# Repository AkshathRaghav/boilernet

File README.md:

# BoilerNet: A Compute-Enabled Mini-NAS

<div align="center" style="display: flex; justify-content: center; align-items: center; gap: 1rem;">

</div>

<div class="caption" align="center">
    BoilerNet Team 20! 
    From L to R: Gokulkrishnan Harikrishnan, Akshath Raghav Ravikiran, Aneesh Reddy Poddutur, Gautum Kottayil Nambiar
</div>

## Overview 

This project aimed to develop a Network Attached Storage utilizing ESP32 MCUs. The aptly-named BoilerNet aims to enable In-Network-compute alongside swappable disks and compute workloads, neatly brought together by a cloud-hosted Dashboard interface. There are a few core ideas that form the foundation for this ”cluster” – Low Power Usage, Plug-and-Play Workloads, High Scalability.

> Our reports/presentations are linked in the [/docs](./docs/). They contain in-depth views, reasonings and explanations regarding the design and its motivation. We also outline how we tested and ensured functionality. **This repository is just meant to help anyone who wishes to "refer" to our code/designs for their own use-case.**

> Watch the Demo that won us the "Senior Design Award" for Spring '25 through Purdue ECE: [Link](https://www.youtube.com/watch?v=jUlh9KClEwE)!

<div style="display: flex; justify-content: center; align-items: center; gap: 1rem;">

</div>
<div class="caption" align="center">
    Top Level System Diagrams
</div>

## Mechanical Design

The physical enclosure consists of six piece types, along with an optional divider: 1x Enclosure Lid, 1x Enclosure Base, 8x compute Enclosures, 8x compute Enclosure Lids, 6x
3mm diameter - 20mm screws, 4x 3mm diameter - 5 mm screws. You can find the related CAD files at [/cad/](./cad/) w/o dependencies. Reach out to [Aneesh Poddutur](https://www.linkedin.com/in/aneesh-poddutur/) for more information. 

<div align="center">
  
  <caption> 
</div>
<div class="caption" align="center">
    Physical Enclosure
</div>

<div align="center">
  
</div>
<div class="caption" align="center">
    Top Enclosure
</div>

<div align="center">
  
</div>
<div class="caption" align="center">
    Compute Enclosure
</div>

<div align="center">
  
</div>
<div class="caption" align="center">
    Assembled System!
</div>

## PCB Design

This was our first time working on PCB Design, and had a few fly-wires hanging about. Below is one of the slides we usd in our [Final Presentation](/docs/Final%20Design%20Review.pdf) to sound endearing ;)

You can find our PCB Designs at [/gerbers/](./gerbers/) and [/kicad_projects](./kicad_projects/)! Reach out to [Gautam Nambiar](https://www.linkedin.com/in/gautam-nambiar-821479251/) and [Gokul Harikrishnan](https://www.linkedin.com/in/gokulkrishnan-harikrishnan-40334b227/) if you have any questions.

<div align="center">
  
</div>
<div class="caption" align="center">
    Network/Switch PCB
</div>

<div align="center">
  
</div>
<div class="caption" align="center">
    Compute Node PCB
</div>

<div align="center">
  
</div>
<div class="caption" align="center">
    Mishaps/Learnings!
</div>

## Software 

All the code for the MCUs are maintained within the [/src](./src/) folder. Each node's build is maintained within it's own ESP-IDF setup, and can be configured in isolation. 
[/model_train](./model_train/) contains the code for training the models and preparing weights to flashed through [./compute_nodes](./src/compute_nodes/). Please reach out to [Akshath Raghav](https://www.linkedin.com/in/akshathrr/) if you have any questions!

- [/src/fastapi_backend](./src/fastapi_backend/) and [/src/streamlit_frontend](./src/streamlit_frontend/) can be configured using the Makefiles. Try `make venv; make setup; make run`. 
- [/src/network_node](./src/network_node/), [/src/switch_nodes](./src/switch_nodes/) and [/src/compute_nodes](./src/compute_nodes/) require `idf.py` configured and `IDF_PATH` set up. Remember, `idf.py` should be run in an ESP-IDF project directory, i.e., a directory containing a CMakeLists.txt file. `idf.py fullclean; idf.py build; idf.py flash -port /dev/ttyUSB1` will be sufficient. 
- [/model_train/extract.sh](./model_train/extract.sh) has the script for setting up ImageNet -- only if you want to train your own subsets. Thanks to [BIGBALLON](https://gist.github.com/BIGBALLON) for this [script](https://gist.github.com/BIGBALLON/8a71d225eff18d88e469e6ea9b39cef4). 
- [/model_train/train.py](./model_train/train.py) and [/model_train/convert_and_header.py](./model_train/convert_and_header.py) will set you up quickly with training your MobileNet or EfficientNet backbones with a head for the subset you've chosen, and then quantizing them (w/ additional calibration tuning). Results will be put into [/model_train/models](./model_train/models/) and [/model_train/quantized_models](./model_train/quantized_models/). After you're done training, put the chosen header (.cc) file into [/src/compute_nodes/main](./src/compute_nodes/main/) and put this file name into Line 5 in [/src/compute_nodes/main/CMakeLists.txt](/src/compute_nodes/main/CMakeLists.txt). 

---

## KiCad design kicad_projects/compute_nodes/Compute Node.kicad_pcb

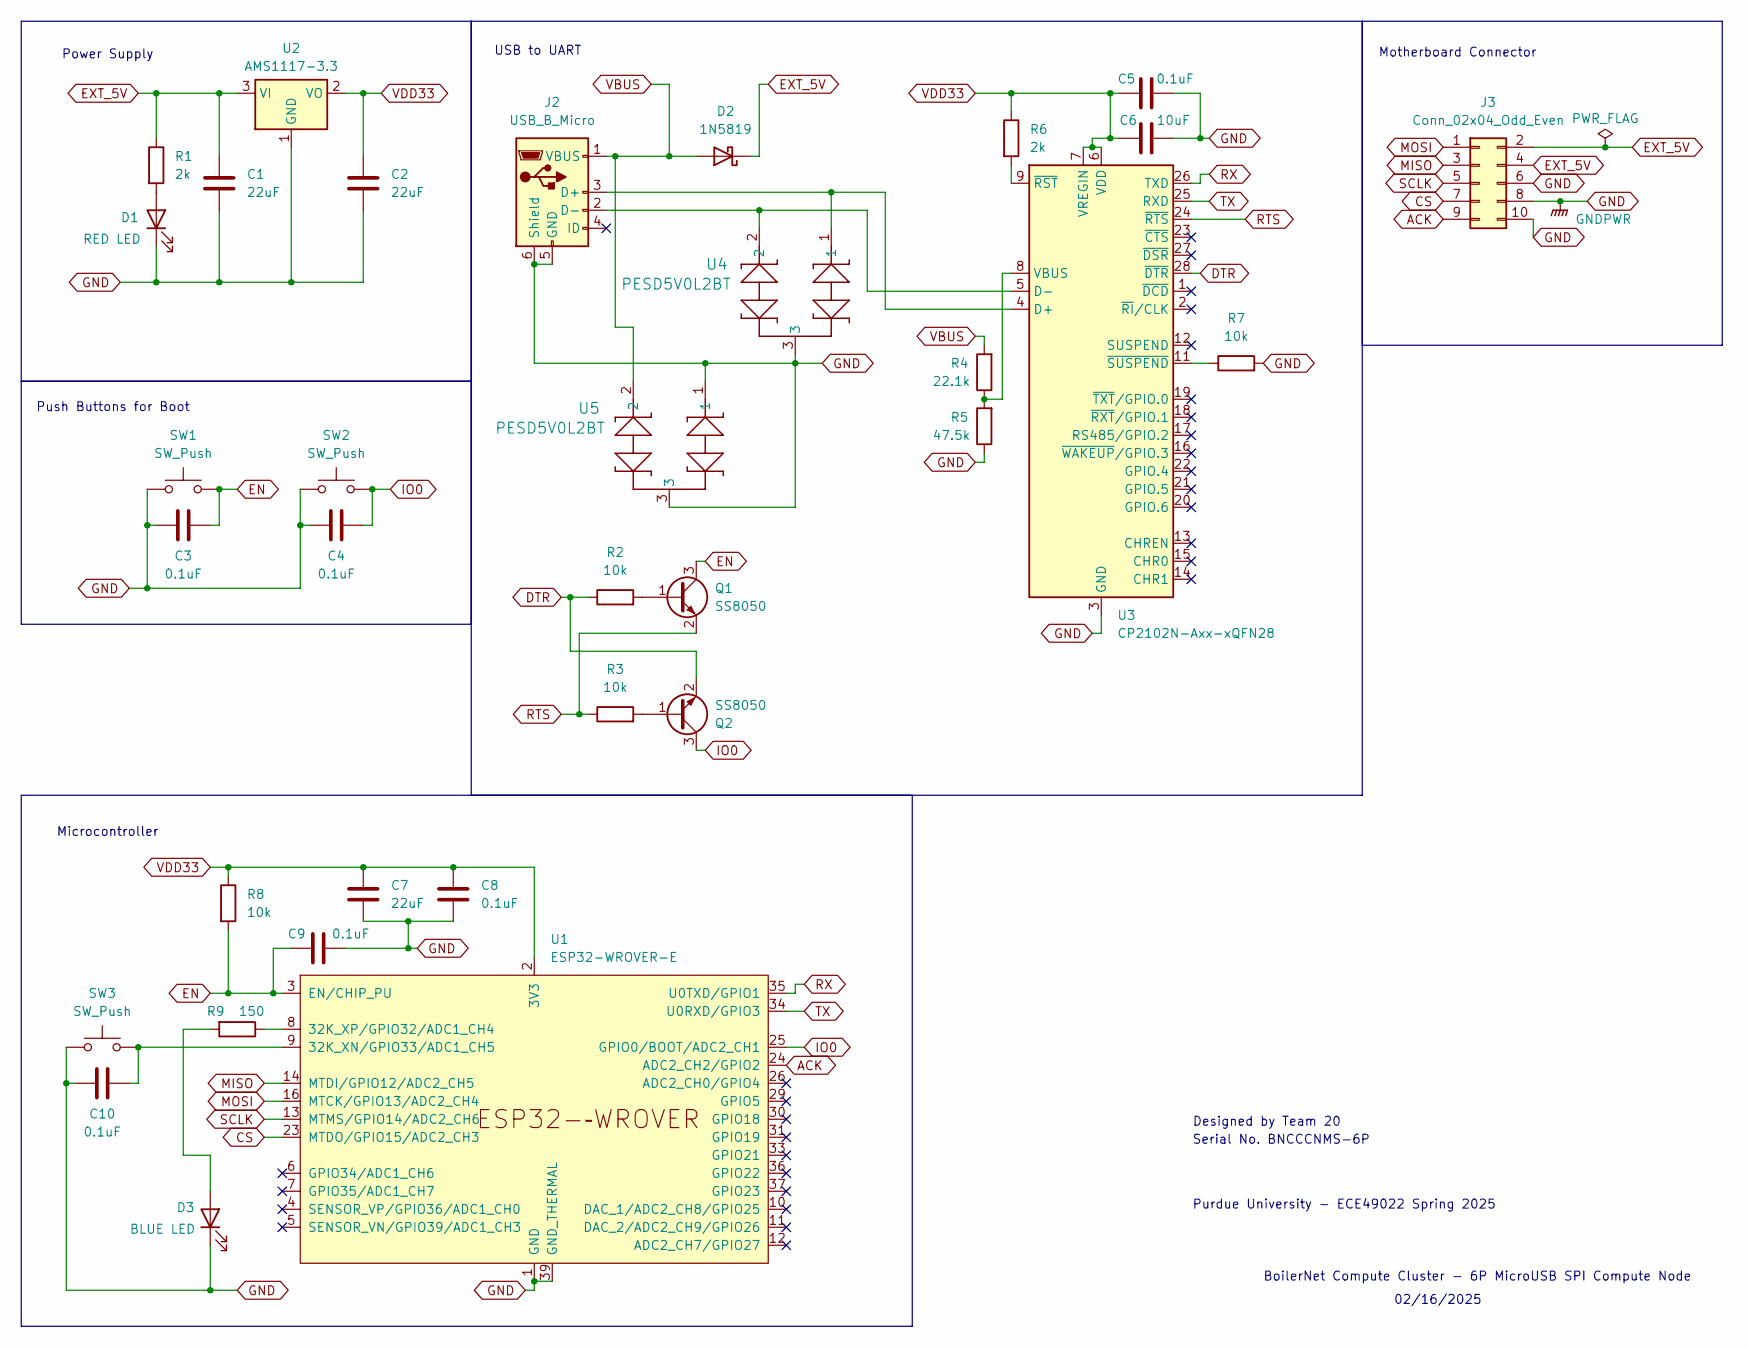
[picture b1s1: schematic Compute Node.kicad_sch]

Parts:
C1, C2, C7: 22uF; C_1206_3216Metric_Pad1.33x1.80mm_HandSolder
C3, C4, C5, C8, C9, C10: 0.1uF; C_1206_3216Metric_Pad1.33x1.80mm_HandSolder
C6: 10uF; C_1206_3216Metric_Pad1.33x1.80mm_HandSolder
D1: RED LED; LED_D4.0mm
D2: 1N5819; D_DO-41_SOD81_P10.16mm_Horizontal
D3: BLUE LED; LED_D4.0mm
J2: USB_B_Micro; USB_Micro-B_Amphenol_10118193-0002LF_Horizontal
J3: Conn_02x04_Odd_Even; PinHeader_2x05_P2.54mm_Horizontal
Q1, Q2: SS8050; SOT-23
R1, R6: 2k; R_1206_3216Metric_Pad1.30x1.75mm_HandSolder
R2, R3, R7, R8: 10k; R_1206_3216Metric_Pad1.30x1.75mm_HandSolder
R4: 22.1k; R_1206_3216Metric_Pad1.30x1.75mm_HandSolder
R5: 47.5k; R_1206_3216Metric_Pad1.30x1.75mm_HandSolder
R9: 150; R_1206_3216Metric_Pad1.30x1.75mm_HandSolder
SW1, SW2, SW3: SW_Push; SW_PUSH_6mm
U1: ESP32-WROVER-E
U2: AMS1117-3.3; SOT-223-3_TabPin2
U3: CP2102N-Axx-xQFN28; QFN-28-1EP_5x5mm_P0.5mm_EP3.35x3.35mm
U4, U5: PESD5V0L2BT; SOT23_NXP-M

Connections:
ACK: J3.9, U1.24 (ADC2_CH2/GPIO2)
CS: J3.7, U1.23 (MTDO/GPIO15/ADC2_CH3)
DTR: Q2.2 (E), R2.1, U3.28 (~DTR)
EN: C3.2, C9.2, Q1.3 (C), R8.2, SW1.2, U1.3 (EN/CHIP_PU)
EXT_5V: C1.1, D2.1 (K), J3.2, J3.4, R1.1, U2.3 (VI)
GND: C1.2, C2.2, C3.1, C4.1, C5.2, C6.2, C7.2, C8.2, C9.1, C10.1, D1.1 (K), D3.1 (K), J2.5 (GND), J2.6 (Shield), J3.6, J3.8, J3.10, R5.1, R7.2, SW1.1, SW2.1, SW3.1, U1.1 (GND), U1.15 (GND), U1.38 (GND), U1.39 (GND_THERMAL), U2.1 (GND), U3.3 (GND), U3.29 (GND), U4.3, U5.1, U5.3
IO0: C4.2, Q2.3 (C), SW2.2, U1.25 (GPIO0/BOOT/ADC2_CH1)
MISO: J3.3, U1.14 (MTDI/GPIO12/ADC2_CH5)
MOSI: J3.1, U1.16 (MTCK/GPIO13/ADC2_CH4)
unnamed: D1.2 (A), R1.2
unnamed: D3.2 (A), R9.2
unnamed: J2.3 (D+), U3.4 (D+), U4.1
unnamed: J2.2 (D-), U3.5 (D-), U4.2
unnamed: Q1.1 (B), R2.2
unnamed: Q2.1 (B), R3.2
unnamed: C10.2, SW3.2, U1.9 (32K_XN/GPIO33/ADC1_CH5)
unnamed: R9.1, U1.8 (32K_XP/GPIO32/ADC1_CH4)
unnamed: R4.1, R5.2, U3.8 (VBUS)
unnamed: R6.2, U3.9 (~RST)
unnamed: R7.1, U3.11 (~SUSPEND)
RTS: Q1.2 (E), R3.1, U3.24 (~RTS)
RX: U1.35 (U0TXD/GPIO1), U3.26 (TXD)
SCLK: J3.5, U1.13 (MTMS/GPIO14/ADC2_CH6)
TX: U1.34 (U0RXD/GPIO3), U3.25 (RXD)
VBUS: D2.2 (A), J2.1 (VBUS), R4.2, U5.2
VDD33: C2.1, C5.1, C6.1, C7.1, C8.1, R6.1, R8.1, U1.2 (3V3), U2.2 (VO), U3.6 (VDD), U3.7 (VREGIN)

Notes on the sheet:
Designed by Team 20
Motherboard Connector
Purdue University - ECE49022 Spring 2025
Microcontroller
USB to UART
Serial No. BNCCCNMS-6P
02/16/2025
Push Buttons for Boot
Power Supply
BoilerNet Compute Cluster - 6P MicroUSB SPI Compute Node

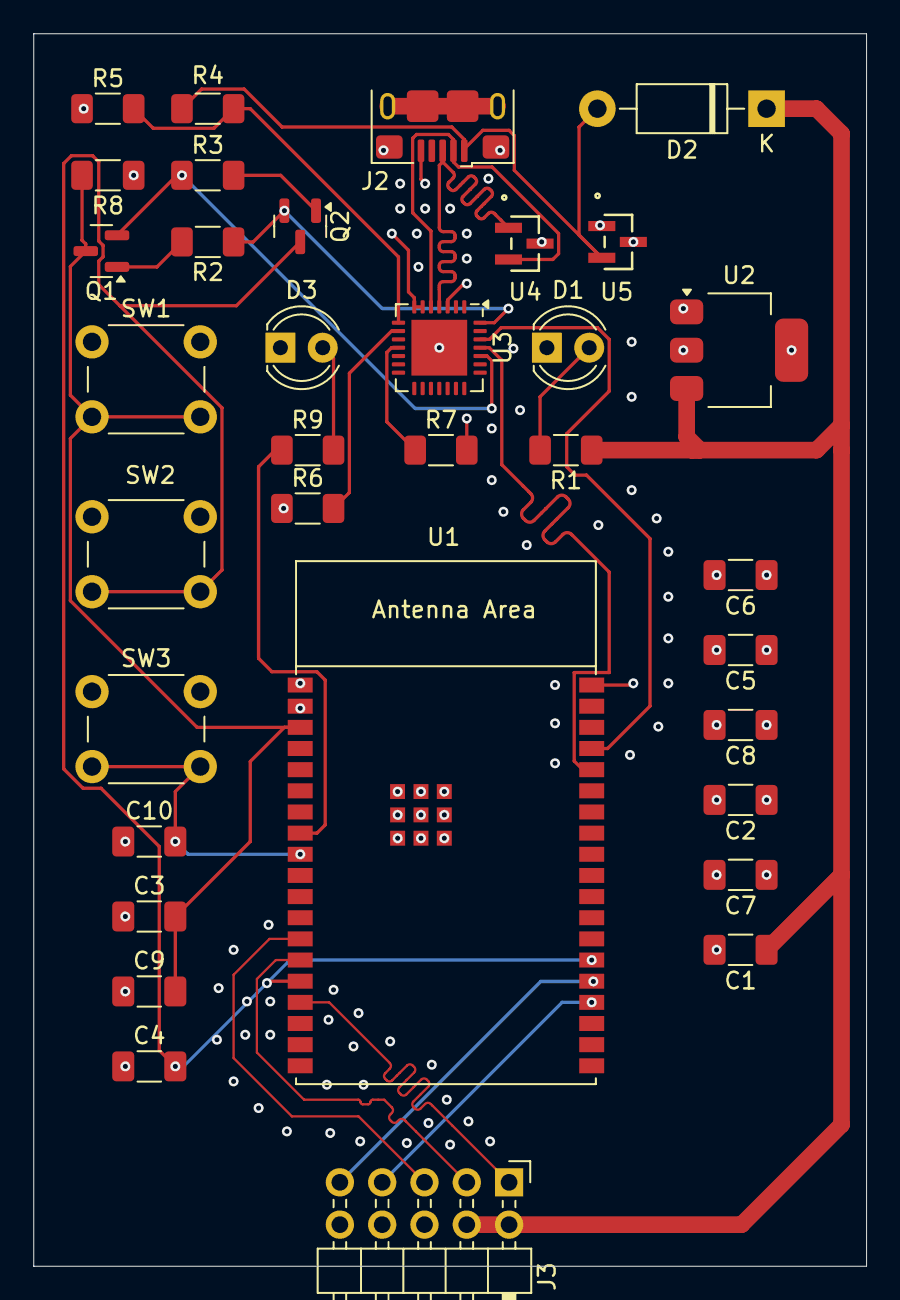
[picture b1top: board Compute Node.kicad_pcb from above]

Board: 4 copper layers, 50.0 x 74.0 mm, 34 parts (0 on the bottom side), 26 nets.

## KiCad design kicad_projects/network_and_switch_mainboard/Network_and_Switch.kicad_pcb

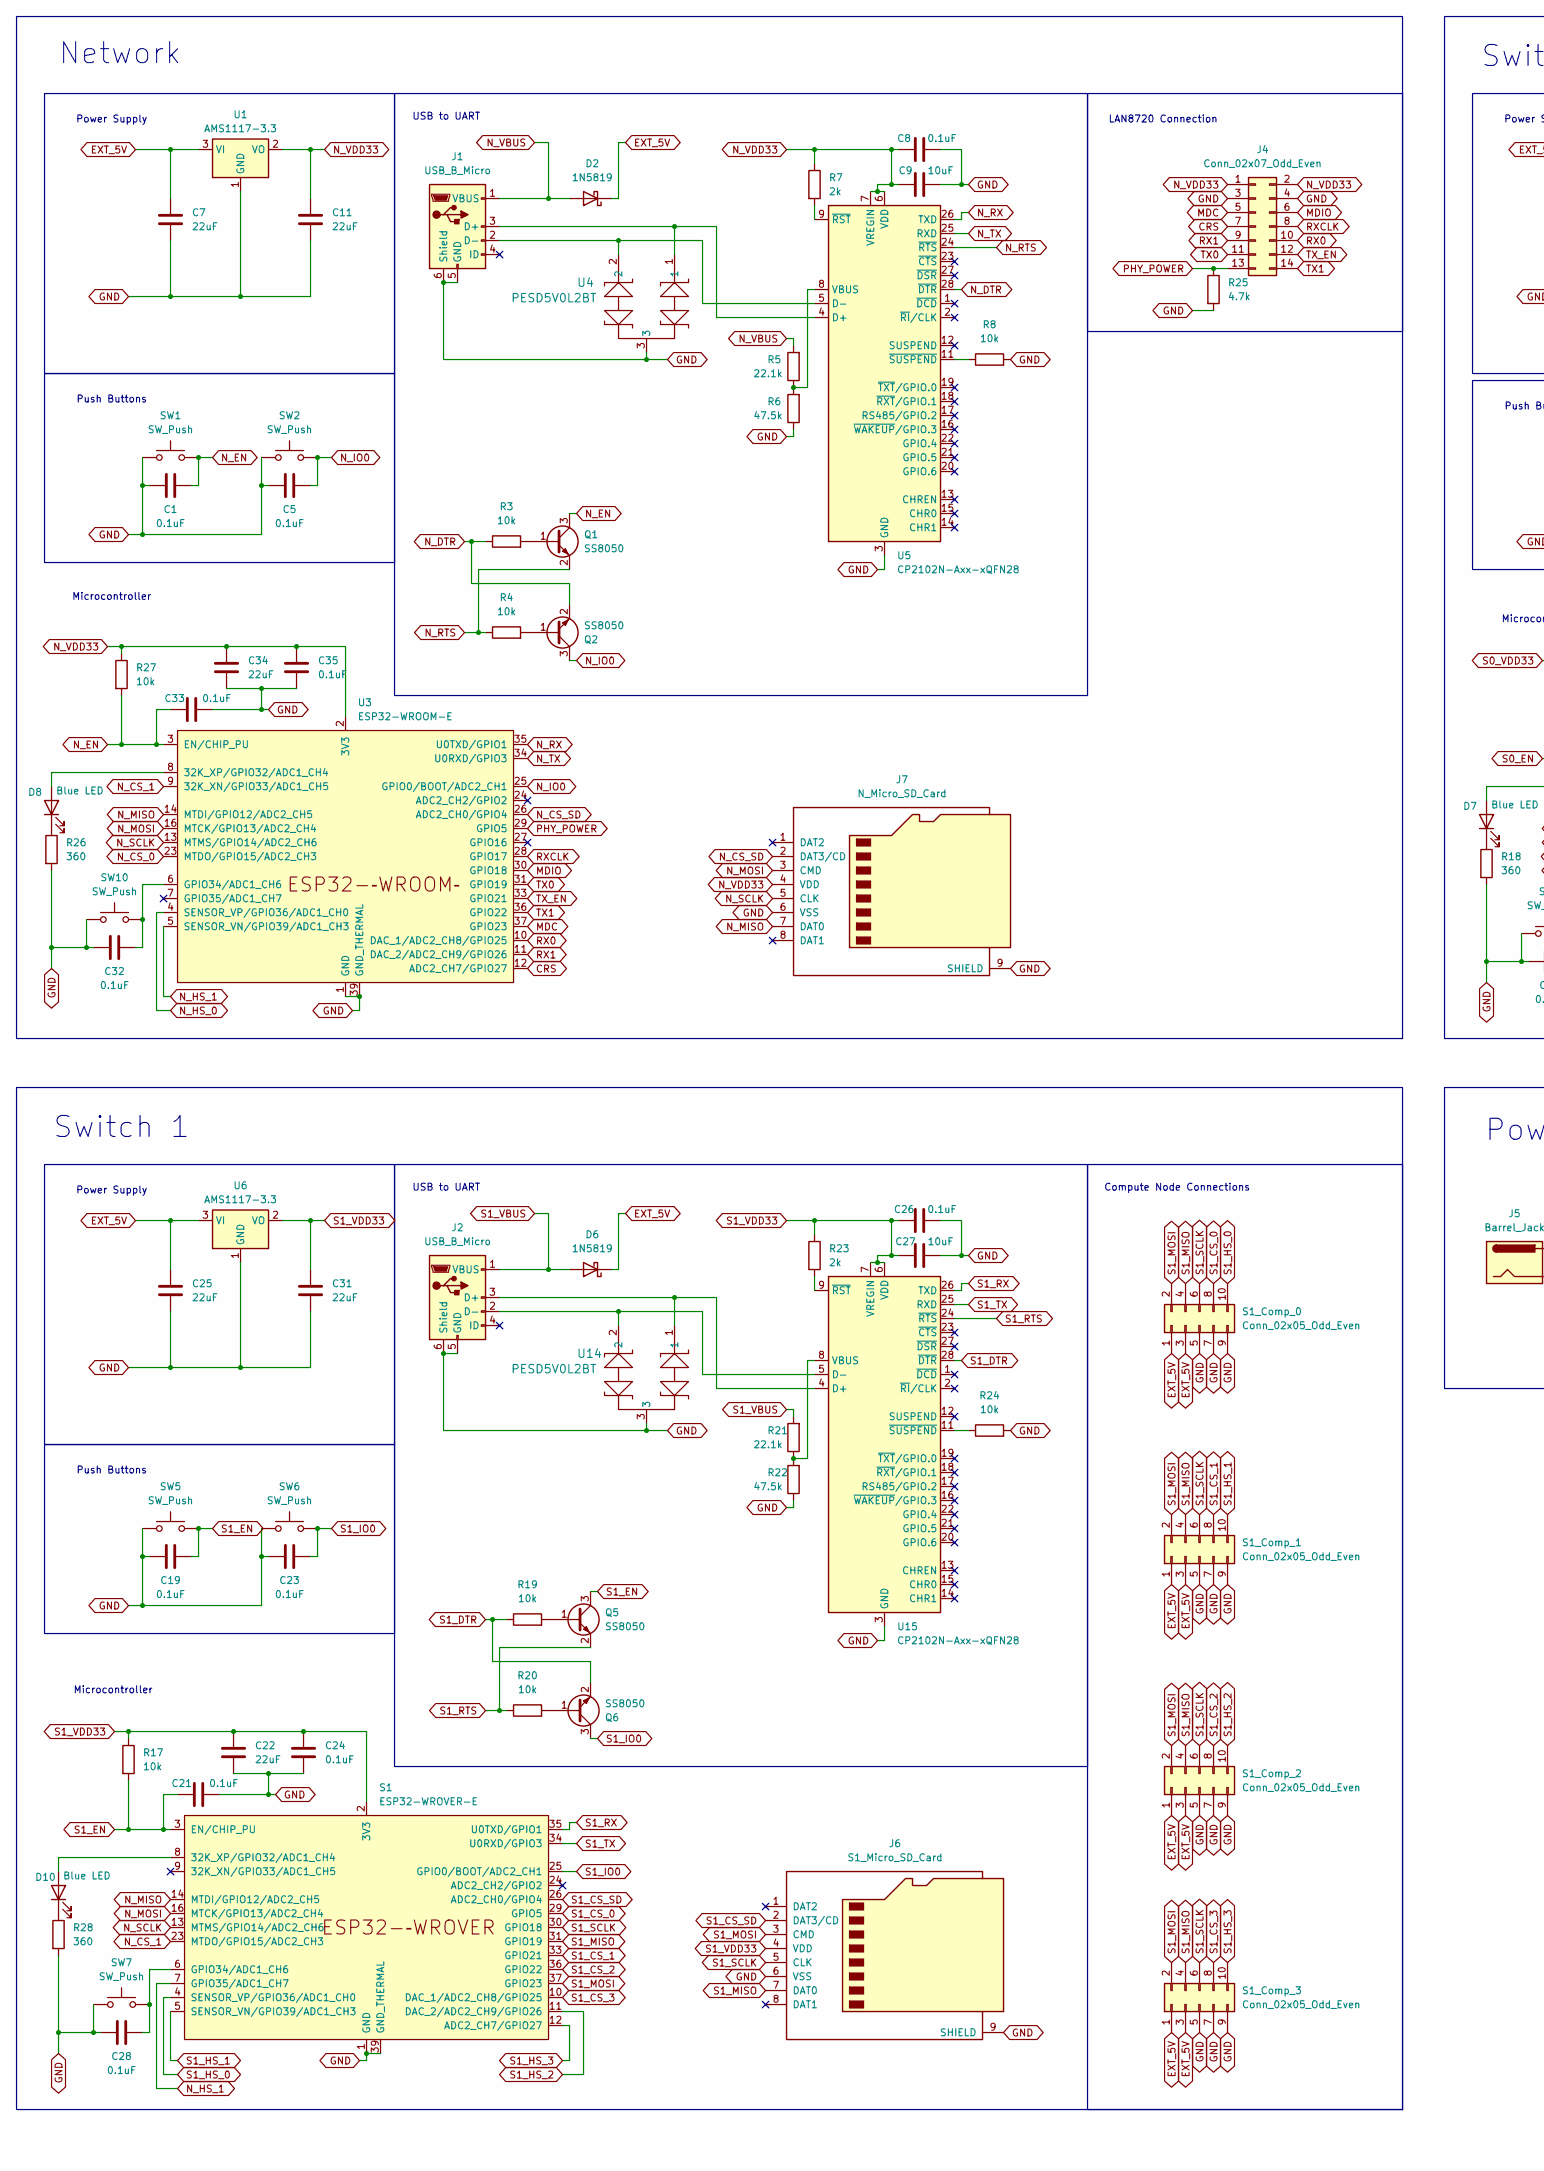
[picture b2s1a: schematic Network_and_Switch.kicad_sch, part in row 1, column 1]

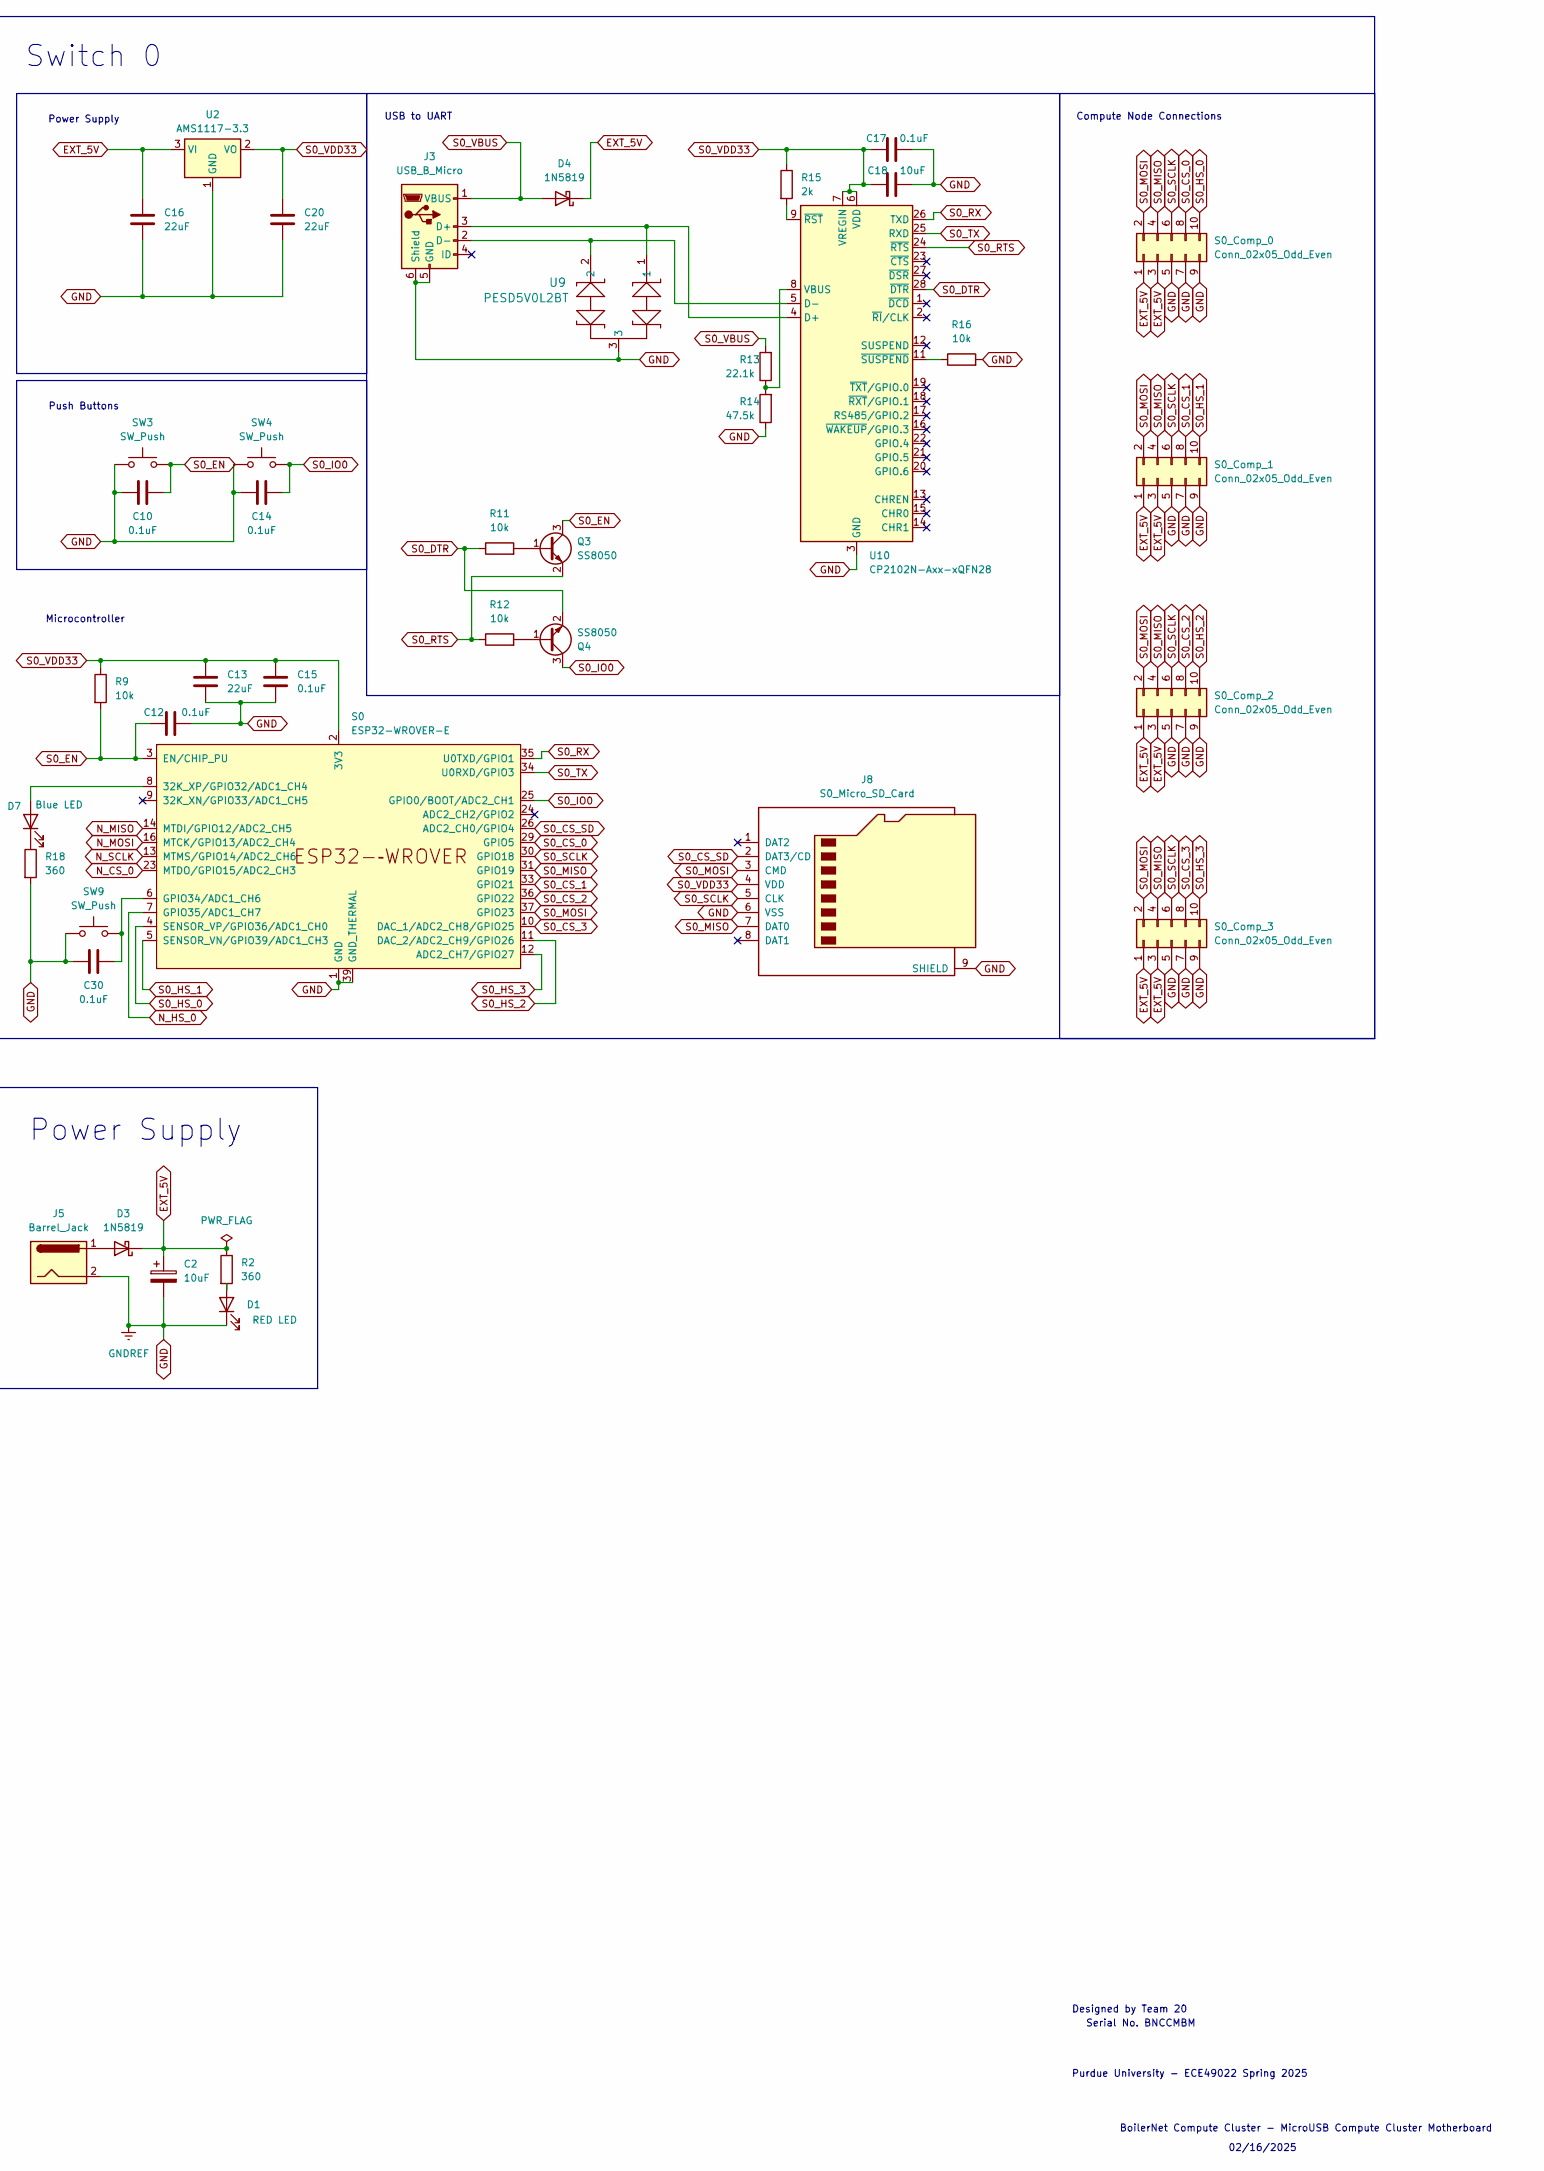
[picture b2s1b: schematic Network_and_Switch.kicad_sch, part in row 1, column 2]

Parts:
C1, C5, C8, C10, C12, C14, C15, C17, C19, C21, C23, C24, C26, C28, C30, C32, C33, C35: 0.1uF; C_1206_3216Metric_Pad1.33x1.80mm_HandSolder
C2, C9, C18, C27: 10uF; C_1206_3216Metric_Pad1.33x1.80mm_HandSolder
C7, C11, C13, C16, C20, C22, C25, C31, C34: 22uF; C_1206_3216Metric_Pad1.33x1.80mm_HandSolder
D1: RED LED; LED_D4.0mm
D2, D3, D4, D6: 1N5819; D_DO-41_SOD81_P10.16mm_Horizontal
D7, D8, D10: Blue LED; LED_D4.0mm
J1, J2, J3: USB_B_Micro; USB_Micro-B_Amphenol_10118193-0002LF_Horizontal
J4: Conn_02x07_Odd_Even; PinHeader_2x07_P2.54mm_Vertical
J5: Barrel_Jack; BarrelJack_CUI_PJ-063AH_Horizontal_CircularHoles
J6: S1_Micro_SD_Card; Samtec_UMPS-07-XX.X-X-V-S_1x07_P2.0mm_Socket
J7: N_Micro_SD_Card; Samtec_UMPS-07-XX.X-X-V-S_1x07_P2.0mm_Socket
J8: S0_Micro_SD_Card; Samtec_UMPS-07-XX.X-X-V-S_1x07_P2.0mm_Socket
Q1, Q2, Q3, Q4, Q5, Q6: SS8050; SOT-23
R2, R18, R26, R28: 360; R_1206_3216Metric_Pad1.30x1.75mm_HandSolder
R3, R4, R8, R9, R11, R12, R16, R17, R19, R20, R24, R27: 10k; R_1206_3216Metric_Pad1.30x1.75mm_HandSolder
R5, R13, R21: 22.1k; R_1206_3216Metric_Pad1.30x1.75mm_HandSolder
R6, R14, R22: 47.5k; R_1206_3216Metric_Pad1.30x1.75mm_HandSolder
R7, R15, R23: 2k; R_1206_3216Metric_Pad1.30x1.75mm_HandSolder
R25: 4.7k; R_1206_3216Metric_Pad1.30x1.75mm_HandSolder
S0, S1: ESP32-WROVER-E
S0_Comp_0, S0_Comp_1, S0_Comp_2, S0_Comp_3, S1_Comp_0, S1_Comp_1, S1_Comp_2, S1_Comp_3: Conn_02x05_Odd_Even; PinHeader_2x05_P2.54mm_Vertical
SW1, SW2, SW3, SW4, SW5, SW6, SW7, SW9, SW10: SW_Push; SW_PUSH_6mm
U1, U2, U6: AMS1117-3.3; SOT-223-3_TabPin2
U3: ESP32-WROOM-E; ESP32-WROOM-32E
U4, U9, U14: PESD5V0L2BT; SOT23_NXP-M
U5, U10, U15: CP2102N-Axx-xQFN28; QFN-28-1EP_5x5mm_P0.5mm_EP3.35x3.35mm

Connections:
CRS: J4.7, U3.12 (ADC2_CH7/GPIO27)
EXT_5V: C2.1, C7.1, C16.1, C25.1, D2.1 (K), D3.1 (K), D4.1 (K), D6.1 (K), R2.1, S0_Comp_0.1, S0_Comp_0.3, S0_Comp_1.1, S0_Comp_1.3, S0_Comp_2.1, S0_Comp_2.3, S0_Comp_3.1, S0_Comp_3.3, S1_Comp_0.1, S1_Comp_0.3, S1_Comp_1.1, S1_Comp_1.3, S1_Comp_2.1, S1_Comp_2.3, S1_Comp_3.1, S1_Comp_3.3, U1.3 (VI), U2.3 (VI), U6.3 (VI)
GND: C1.1, C2.2, C5.1, C7.2, C8.2, C9.2, C10.1, C11.2, C12.1, C13.2, C14.1, C15.2, C16.2, C17.2, C18.2, C19.1, C20.2, C21.1, C22.2, C23.1, C24.2, C25.2, C26.2, C27.2, C28.1, C30.1, C31.2, C32.1, C33.1, C34.2, C35.2, D1.1 (K), J1.5 (GND), J1.6 (Shield), J2.5 (GND), J2.6 (Shield), J3.5 (GND), J3.6 (Shield), J4.3, J4.4, J5.2, J6.6 (VSS), J6.9 (SHIELD), J7.6 (VSS), J7.9 (SHIELD), J8.6 (VSS), J8.9 (SHIELD), R6.1, R8.2, R14.1, R16.2, R18.2, R22.1, R24.2, R25.2, R26.2, R28.2, S0.1 (GND), S0.15 (GND), S0.38 (GND), S0.39 (GND_THERMAL), S0_Comp_0.5, S0_Comp_0.7, S0_Comp_0.9, S0_Comp_1.5, S0_Comp_1.7, S0_Comp_1.9, S0_Comp_2.5, S0_Comp_2.7, S0_Comp_2.9, S0_Comp_3.5, S0_Comp_3.7, S0_Comp_3.9, S1.1 (GND), S1.15 (GND), S1.38 (GND), S1.39 (GND_THERMAL), S1_Comp_0.5, S1_Comp_0.7, S1_Comp_0.9, S1_Comp_1.5, S1_Comp_1.7, S1_Comp_1.9, S1_Comp_2.5, S1_Comp_2.7, S1_Comp_2.9, S1_Comp_3.5, S1_Comp_3.7, S1_Comp_3.9, SW1.1, SW2.1, SW3.1, SW4.1, SW5.1, SW6.1, SW7.1, SW9.1, SW10.1, U1.1 (GND), U2.1 (GND), U3.1 (GND), U3.15 (GND), U3.38 (GND), U3.39 (GND_THERMAL), U4.3, U5.3 (GND), U5.29 (GND), U6.1 (GND), U9.3, U10.3 (GND), U10.29 (GND), U14.3, U15.3 (GND), U15.29 (GND)
MDC: J4.5, U3.37 (GPIO23)
MDIO: J4.6, U3.30 (GPIO18)
N_CS_0: S0.23 (MTDO/GPIO15/ADC2_CH3), U3.23 (MTDO/GPIO15/ADC2_CH3)
N_CS_1: S1.23 (MTDO/GPIO15/ADC2_CH3), U3.9 (32K_XN/GPIO33/ADC1_CH5)
N_CS_SD: J7.2 (DAT3/CD), U3.26 (ADC2_CH0/GPIO4)
N_DTR: Q2.2 (E), R3.1, U5.28 (~DTR)
N_EN: C1.2, C33.2, Q1.3 (C), R27.2, SW1.2, U3.3 (EN/CHIP_PU)
N_HS_0: S0.7 (GPIO35/ADC1_CH7), U3.4 (SENSOR_VP/GPIO36/ADC1_CH0)
N_HS_1: S1.7 (GPIO35/ADC1_CH7), U3.5 (SENSOR_VN/GPIO39/ADC1_CH3)
N_IO0: C5.2, Q2.3 (C), SW2.2, U3.25 (GPIO0/BOOT/ADC2_CH1)
N_MISO: J7.7 (DAT0), S0.14 (MTDI/GPIO12/ADC2_CH5), S1.14 (MTDI/GPIO12/ADC2_CH5), U3.14 (MTDI/GPIO12/ADC2_CH5)
N_MOSI: J7.3 (CMD), S0.16 (MTCK/GPIO13/ADC2_CH4), S1.16 (MTCK/GPIO13/ADC2_CH4), U3.16 (MTCK/GPIO13/ADC2_CH4)
N_RTS: Q1.2 (E), R4.1, U5.24 (~RTS)
N_RX: U3.35 (U0TXD/GPIO1), U5.26 (TXD)
N_SCLK: J7.5 (CLK), S0.13 (MTMS/GPIO14/ADC2_CH6), S1.13 (MTMS/GPIO14/ADC2_CH6), U3.13 (MTMS/GPIO14/ADC2_CH6)
N_TX: U3.34 (U0RXD/GPIO3), U5.25 (RXD)
N_VBUS: D2.2 (A), J1.1 (VBUS), R5.2
N_VDD33: C8.1, C9.1, C11.1, C34.1, C35.1, J4.1, J4.2, J7.4 (VDD), R7.1, R27.1, U1.2 (VO), U3.2 (3V3), U5.6 (VDD), U5.7 (VREGIN)
unnamed: D1.2 (A), R2.2
unnamed: D3.2 (A), J5.1
unnamed: D7.2 (A), S0.8 (32K_XP/GPIO32/ADC1_CH4)
unnamed: D7.1 (K), R18.1
unnamed: D8.2 (A), U3.8 (32K_XP/GPIO32/ADC1_CH4)
unnamed: D8.1 (K), R26.1
unnamed: D10.2 (A), S1.8 (32K_XP/GPIO32/ADC1_CH4)
unnamed: D10.1 (K), R28.1
unnamed: J1.3 (D+), U4.1, U5.4 (D+)
unnamed: J1.2 (D-), U4.2, U5.5 (D-)
unnamed: J2.3 (D+), U14.1, U15.4 (D+)
unnamed: J2.2 (D-), U14.2, U15.5 (D-)
unnamed: J3.3 (D+), U9.1, U10.4 (D+)
unnamed: J3.2 (D-), U9.2, U10.5 (D-)
unnamed: Q1.1 (B), R3.2
unnamed: Q2.1 (B), R4.2
unnamed: Q3.1 (B), R11.2
unnamed: Q4.1 (B), R12.2
unnamed: Q5.1 (B), R19.2
unnamed: Q6.1 (B), R20.2
unnamed: C30.2, S0.6 (GPIO34/ADC1_CH6), SW9.2
unnamed: C28.2, S1.6 (GPIO34/ADC1_CH6), SW7.2
unnamed: C32.2, SW10.2, U3.6 (GPIO34/ADC1_CH6)
unnamed: R5.1, R6.2, U5.8 (VBUS)
unnamed: R7.2, U5.9 (~RST)
unnamed: R8.1, U5.11 (~SUSPEND)
unnamed: R13.1, R14.2, U10.8 (VBUS)
unnamed: R15.2, U10.9 (~RST)
unnamed: R16.1, U10.11 (~SUSPEND)
unnamed: R21.1, R22.2, U15.8 (VBUS)
unnamed: R23.2, U15.9 (~RST)
unnamed: R24.1, U15.11 (~SUSPEND)
PHY_POWER: J4.13, R25.1, U3.29 (GPIO5)
RX0: J4.10, U3.10 (DAC_1/ADC2_CH8/GPIO25)
RX1: J4.9, U3.11 (DAC_2/ADC2_CH9/GPIO26)
RXCLK: J4.8, U3.28 (GPIO17)
S0_CS_0: S0.29 (GPIO5), S0_Comp_0.8
S0_CS_1: S0.33 (GPIO21), S0_Comp_1.8
S0_CS_2: S0.36 (GPIO22), S0_Comp_2.8
S0_CS_3: S0.10 (DAC_1/ADC2_CH8/GPIO25), S0_Comp_3.8
S0_CS_SD: J8.2 (DAT3/CD), S0.26 (ADC2_CH0/GPIO4)
S0_DTR: Q4.2 (E), R11.1, U10.28 (~DTR)
S0_EN: C10.2, C12.2, Q3.3 (C), R9.2, S0.3 (EN/CHIP_PU), SW3.2
S0_HS_0: S0.4 (SENSOR_VP/GPIO36/ADC1_CH0), S0_Comp_0.10
S0_HS_1: S0.5 (SENSOR_VN/GPIO39/ADC1_CH3), S0_Comp_1.10
S0_HS_2: S0.11 (DAC_2/ADC2_CH9/GPIO26), S0_Comp_2.10
S0_HS_3: S0.12 (ADC2_CH7/GPIO27), S0_Comp_3.10
S0_IO0: C14.2, Q4.3 (C), S0.25 (GPIO0/BOOT/ADC2_CH1), SW4.2
S0_MISO: J8.7 (DAT0), S0.31 (GPIO19), S0_Comp_0.4, S0_Comp_1.4, S0_Comp_2.4, S0_Comp_3.4
S0_MOSI: J8.3 (CMD), S0.37 (GPIO23), S0_Comp_0.2, S0_Comp_1.2, S0_Comp_2.2, S0_Comp_3.2
S0_RTS: Q3.2 (E), R12.1, U10.24 (~RTS)
S0_RX: S0.35 (U0TXD/GPIO1), U10.26 (TXD)
S0_SCLK: J8.5 (CLK), S0.30 (GPIO18), S0_Comp_0.6, S0_Comp_1.6, S0_Comp_2.6, S0_Comp_3.6
S0_TX: S0.34 (U0RXD/GPIO3), U10.25 (RXD)
S0_VBUS: D4.2 (A), J3.1 (VBUS), R13.2
S0_VDD33: C13.1, C15.1, C17.1, C18.1, C20.1, J8.4 (VDD), R9.1, R15.1, S0.2 (3V3), U2.2 (VO), U10.6 (VDD), U10.7 (VREGIN)
S1_CS_0: S1.29 (GPIO5), S1_Comp_0.8
S1_CS_1: S1.33 (GPIO21), S1_Comp_1.8
S1_CS_2: S1.36 (GPIO22), S1_Comp_2.8
S1_CS_3: S1.10 (DAC_1/ADC2_CH8/GPIO25), S1_Comp_3.8
S1_CS_SD: J6.2 (DAT3/CD), S1.26 (ADC2_CH0/GPIO4)
S1_DTR: Q6.2 (E), R19.1, U15.28 (~DTR)
S1_EN: C19.2, C21.2, Q5.3 (C), R17.2, S1.3 (EN/CHIP_PU), SW5.2
S1_HS_0: S1.4 (SENSOR_VP/GPIO36/ADC1_CH0), S1_Comp_0.10
S1_HS_1: S1.5 (SENSOR_VN/GPIO39/ADC1_CH3), S1_Comp_1.10
S1_HS_2: S1.11 (DAC_2/ADC2_CH9/GPIO26), S1_Comp_2.10
S1_HS_3: S1.12 (ADC2_CH7/GPIO27), S1_Comp_3.10
S1_IO0: C23.2, Q6.3 (C), S1.25 (GPIO0/BOOT/ADC2_CH1), SW6.2
S1_MISO: J6.7 (DAT0), S1.31 (GPIO19), S1_Comp_0.4, S1_Comp_1.4, S1_Comp_2.4, S1_Comp_3.4
S1_MOSI: J6.3 (CMD), S1.37 (GPIO23), S1_Comp_0.2, S1_Comp_1.2, S1_Comp_2.2, S1_Comp_3.2
S1_RTS: Q5.2 (E), R20.1, U15.24 (~RTS)
S1_RX: S1.35 (U0TXD/GPIO1), U15.26 (TXD)
S1_SCLK: J6.5 (CLK), S1.30 (GPIO18), S1_Comp_0.6, S1_Comp_1.6, S1_Comp_2.6, S1_Comp_3.6
S1_TX: S1.34 (U0RXD/GPIO3), U15.25 (RXD)
S1_VBUS: D6.2 (A), J2.1 (VBUS), R21.2
S1_VDD33: C22.1, C24.1, C26.1, C27.1, C31.1, J6.4 (VDD), R17.1, R23.1, S1.2 (3V3), U6.2 (VO), U15.6 (VDD), U15.7 (VREGIN)
TX0: J4.11, U3.31 (GPIO19)
TX1: J4.14, U3.36 (GPIO22)
TX_EN: J4.12, U3.33 (GPIO21)

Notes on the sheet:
Power Supply
Microcontroller
Designed by Team 20
USB to UART
Push Buttons
Compute Node Connections
Power Supply
Serial No. BNCCMBM
Switch 0
Switch 1
02/16/2025
Network
BoilerNet Compute Cluster - MicroUSB Compute Cluster Motherboard
LAN8720 Connection
Purdue University - ECE49022 Spring 2025

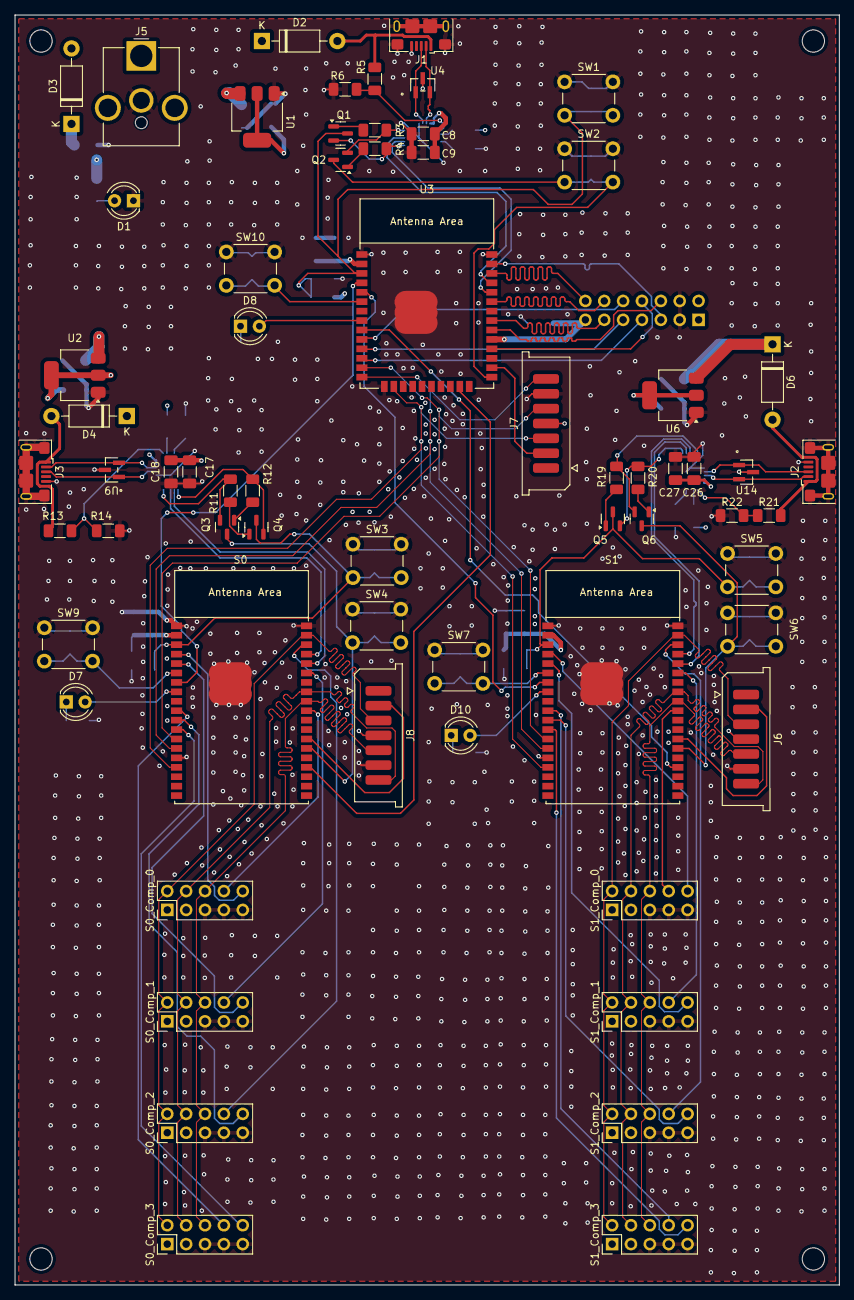
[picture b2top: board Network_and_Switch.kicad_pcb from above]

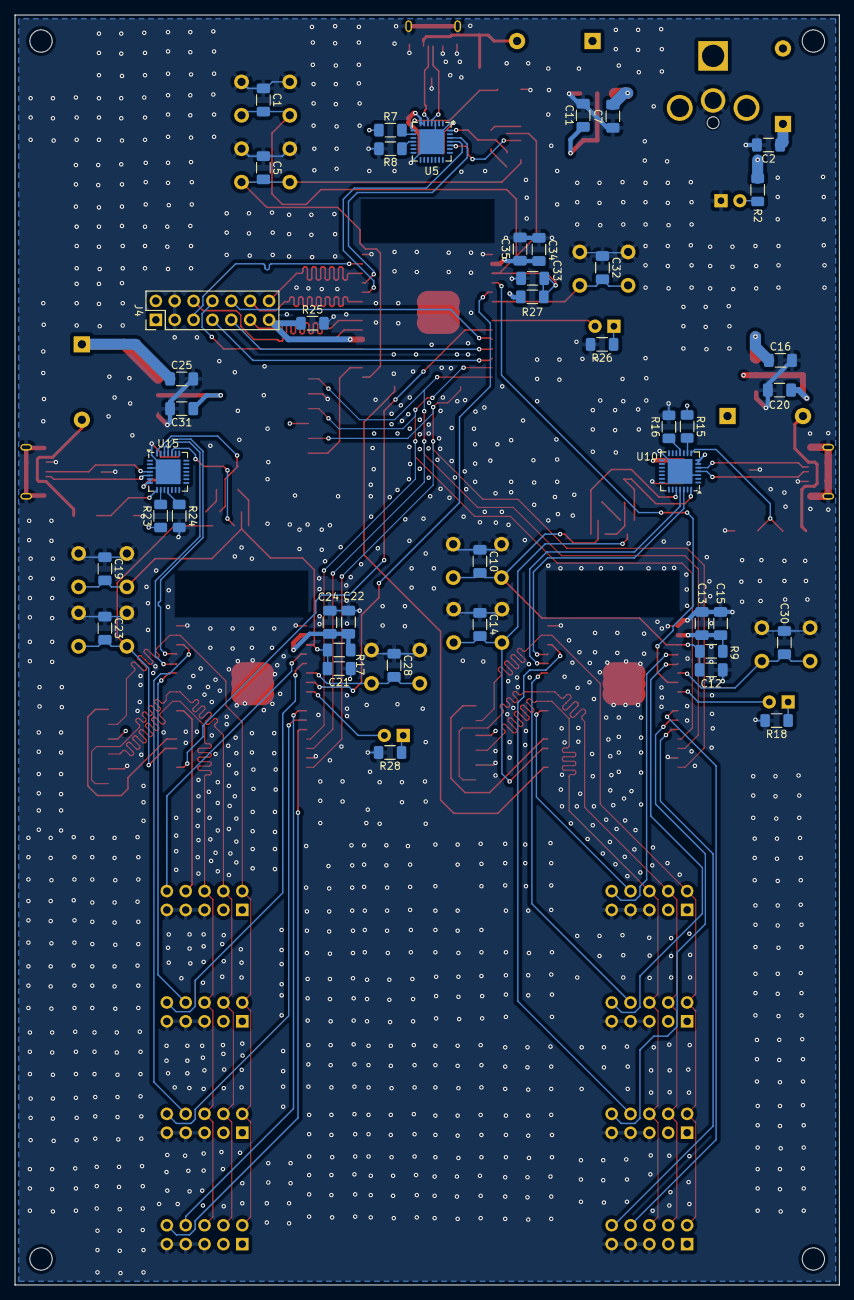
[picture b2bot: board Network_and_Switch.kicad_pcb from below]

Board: 4 copper layers, 111.0 x 171.0 mm, 108 parts (43 on the bottom side), 100 nets.

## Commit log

2025-01-27 Confirmed working
2025-01-30 Initial test branch commit
2025-02-05 test
2025-02-05 Two way usb-uart
2025-02-06 Working
2025-02-06 gitignore
2025-02-06 working back and forth
2025-02-07 Added example SPI sender and receiver
2025-02-16 maybe fix
2025-02-18 commented out the SW stuff. Line 114 tries to EXPECT CLOCK FROM LAN, which is Sautter's workaround - WROVER
2025-03-04 completed
2025-03-04 Minor changes
2025-03-05 Added initial network code
2025-03-05 working on the ETH_SPI stuff
2025-03-05 latest
2025-03-05 updating with the fixed 2-step read/write logic
2025-03-23 finally this shit works master slave talking with actual changing commands
2025-03-23 max i cud do was 5mhz and 50ms delay
2025-03-26 working, but need to add a CRC thing
2025-03-26 need to properly integrate crc, we can ignore the complex confirmation logic by confirming crc one-shot in the slave
2025-04-04 working on the SD card
2025-04-08 writing working with out retry
2025-04-09 WRITING AND READING BOTH WORK GODDAMN
2025-04-11 blueprin for compute set up, now need to do the literal patching of data
2025-04-28 cleaning up
2025-04-28 trained models
2025-04-28 network SD card + delete
2025-04-28 adding models
2025-04-30 current
2025-05-02 edits
2025-05-02 before demo
2025-06-05 final
